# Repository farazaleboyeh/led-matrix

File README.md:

# Custom-Built Music Display

## Goal
The purpose of this project has been to extend my skills as a hardware engineer, specifically in regards to the development of embedded systems. Thus, I challenged myself to build a complete system from scratch that encompasses the entire development lifecycle. From schematic design and PCB layout in KiCad, to writing the C++ firmware for Wi-Fi networking, memory management, & custom LED multiplexing.

## Overview
Repository includes the firmwmare used to show the artwork of a currently streaming song from Spotify onto a custom-built 10x10 display, as well as all primary KiCad project files used to design the system itself. Some examples images of the display in its most recent state are available below.

<div align="center">
  <table>
    <tr>
      <td align="center">
        
        <br />
        <sub><em>Example 1, raw LEDs exposed.</em></sub>
      </td>
      <td align="center">
        
        <br />
        <sub><em>Example 2, raw LEDs exposed.</em></sub>
      </td>
    </tr>
    <tr>
      <td align="center">
        
        <br />
        <sub><em>Example 3, makeshift diffuser overlayed. </em></sub>
      </td>
      <td align="center">
      
        <br />
        <sub><em>Example 4, makeshift diffuser overlayed.</em></sub>
      </td>
    </tr>
  </table>
</div>

The system works by first calling Spotify's APIs to fetch all data regarding the user's playing music. From the given information, a link to the  album art is then used to store all JPEG data (as a stream of bytes) to an internal buffer. The TJpg Decoder library is used to decode the buffer as RGB565 data (locally), which perpetually reaches out to a separate callback function, which converts again to RGB888 and also writes to the display's back framebuffer. When the front and back framebuffers are swapped, a continuously firing interrupt displays the artwork by streaming the bitplanes (sequentially by time slice and physical row), to the display's shift registers. 

## Hardware 
### Comprehensive Component List
* 100 RGB LEDs, multiplexed
* 10 100Ω, 10 150Ω, 10 220Ω, & 10 1kΩ resistors
* 5 (74HC595) shift registers, daisy-chained.
* 10 PNP BJTs
* An ESP32-S3, development board
* A USB-C breakout board

### Core Physical Functionality
The display is driven by an ESP32 microcontroller, which is responsible for streaming color data to the chained shift registers, among other tasks. Transistors are present along all rows which act as high-side power switches between the main power rail and the shared anodes, so that the (output-limited) shift registers are not solely responsible for driving entire rows themselves. 1kΩ current-limiting resistors are present along rows to protect the shift registers and LEDs from overheating & overcurrent, with per-color resistors along each column to finely tune color output (100Ω for red columns, 150Ω, green, & 220Ω blue). Images of the schematic, PCB design, & soldered board are all shown below for reference.

<div align="center">
  
  <br />
  <sub><i>Schematic diagram, designed in KiCad.</i></sub>
</div>

<br />

<div align="center">
  
  <br />
  <sub><i>PCB layout, designed in KiCad.</i></sub>
</div>

<br />

<div align="center">
  
  <br />
  <sub><i>Soldered PCB, note that the breakout is still missing the screws and washers necessary for securing it to the board but is otherwise complete.</i></sub>
</div>

## Firmware 
### Core Logical Functionality

<div align="center">
  
  <br />
  <sub><i>UML sequence diagram, complete program flow.</i></sub>
</div>

### API Access
The basis of the project lies in interfacing with Spotify's APIs to receieve user data regarding their currently playing music. Every time the program begins running, and after a successful Wi-Fi connection is established, one of the first tasks to run is the retrieval of a new Access Token from Spotify's servers. As per the Spotify's requirements, Access Tokens are inherently ephemeral, expiring automatically every 3600 seconds (1 hour) regardless of scope. Thus, a function runs every 55 minutes to renew the Activation Token automatically, ensuring the display can be used for extended periods of time. 

There is not currently, however, any avenue for renewing the Refresh Tokens  automatically at the time of writing. Given they expire every 4 months, an implementation for such was not listed as high-enough priority but is in the works. 

### Interrupt-Driven Binary Code Modulation (BCM)
Instead of standard PWM, which would demand an unsustainable 2,550 SPI updates per frame (10 rows x 255 steps) and cause severe CPU starvation, the driver implements Binary Code Modulation via the microcontroller's hardware timer. By shifting only 8 exponentially weighted bitplanes per row (5µs, 10µs, 20µs, etc.), BCM slashes bus traffic by 97% to just 80 updates per frame, reconstructing full 8-bit color depth through visual persistence while leaving the CPU free for WiFi and JPEG decoding.

### Double Buffering
To prevent screen tearing during WiFi fetches or JPEG decoding: Operations draw to a back framebuffer (`draw_buffer`), `display.swap()` unpacks the back buffer into physical bitplanes (`bitplanes[10][8][5]`), & the ISR (`on_timer`) exclusively reads from the active bitplanes.

## Progress
A list of the main tasks in progress for this project:
* Upscaling the 8x8 artwork to 10x10
* Implementing animated song transitions
* Designing and 3D printing an enlosure and diffuser

A non-exhaustive list of ideas for future iterations of this project:
* LEDs & all other display hardware sitting on separate PCBs
* Playback controls (buttons, or other sensors for touchless playback)
* Transition firmware from Arduino framework to ESP-IDF with FreeRTOS

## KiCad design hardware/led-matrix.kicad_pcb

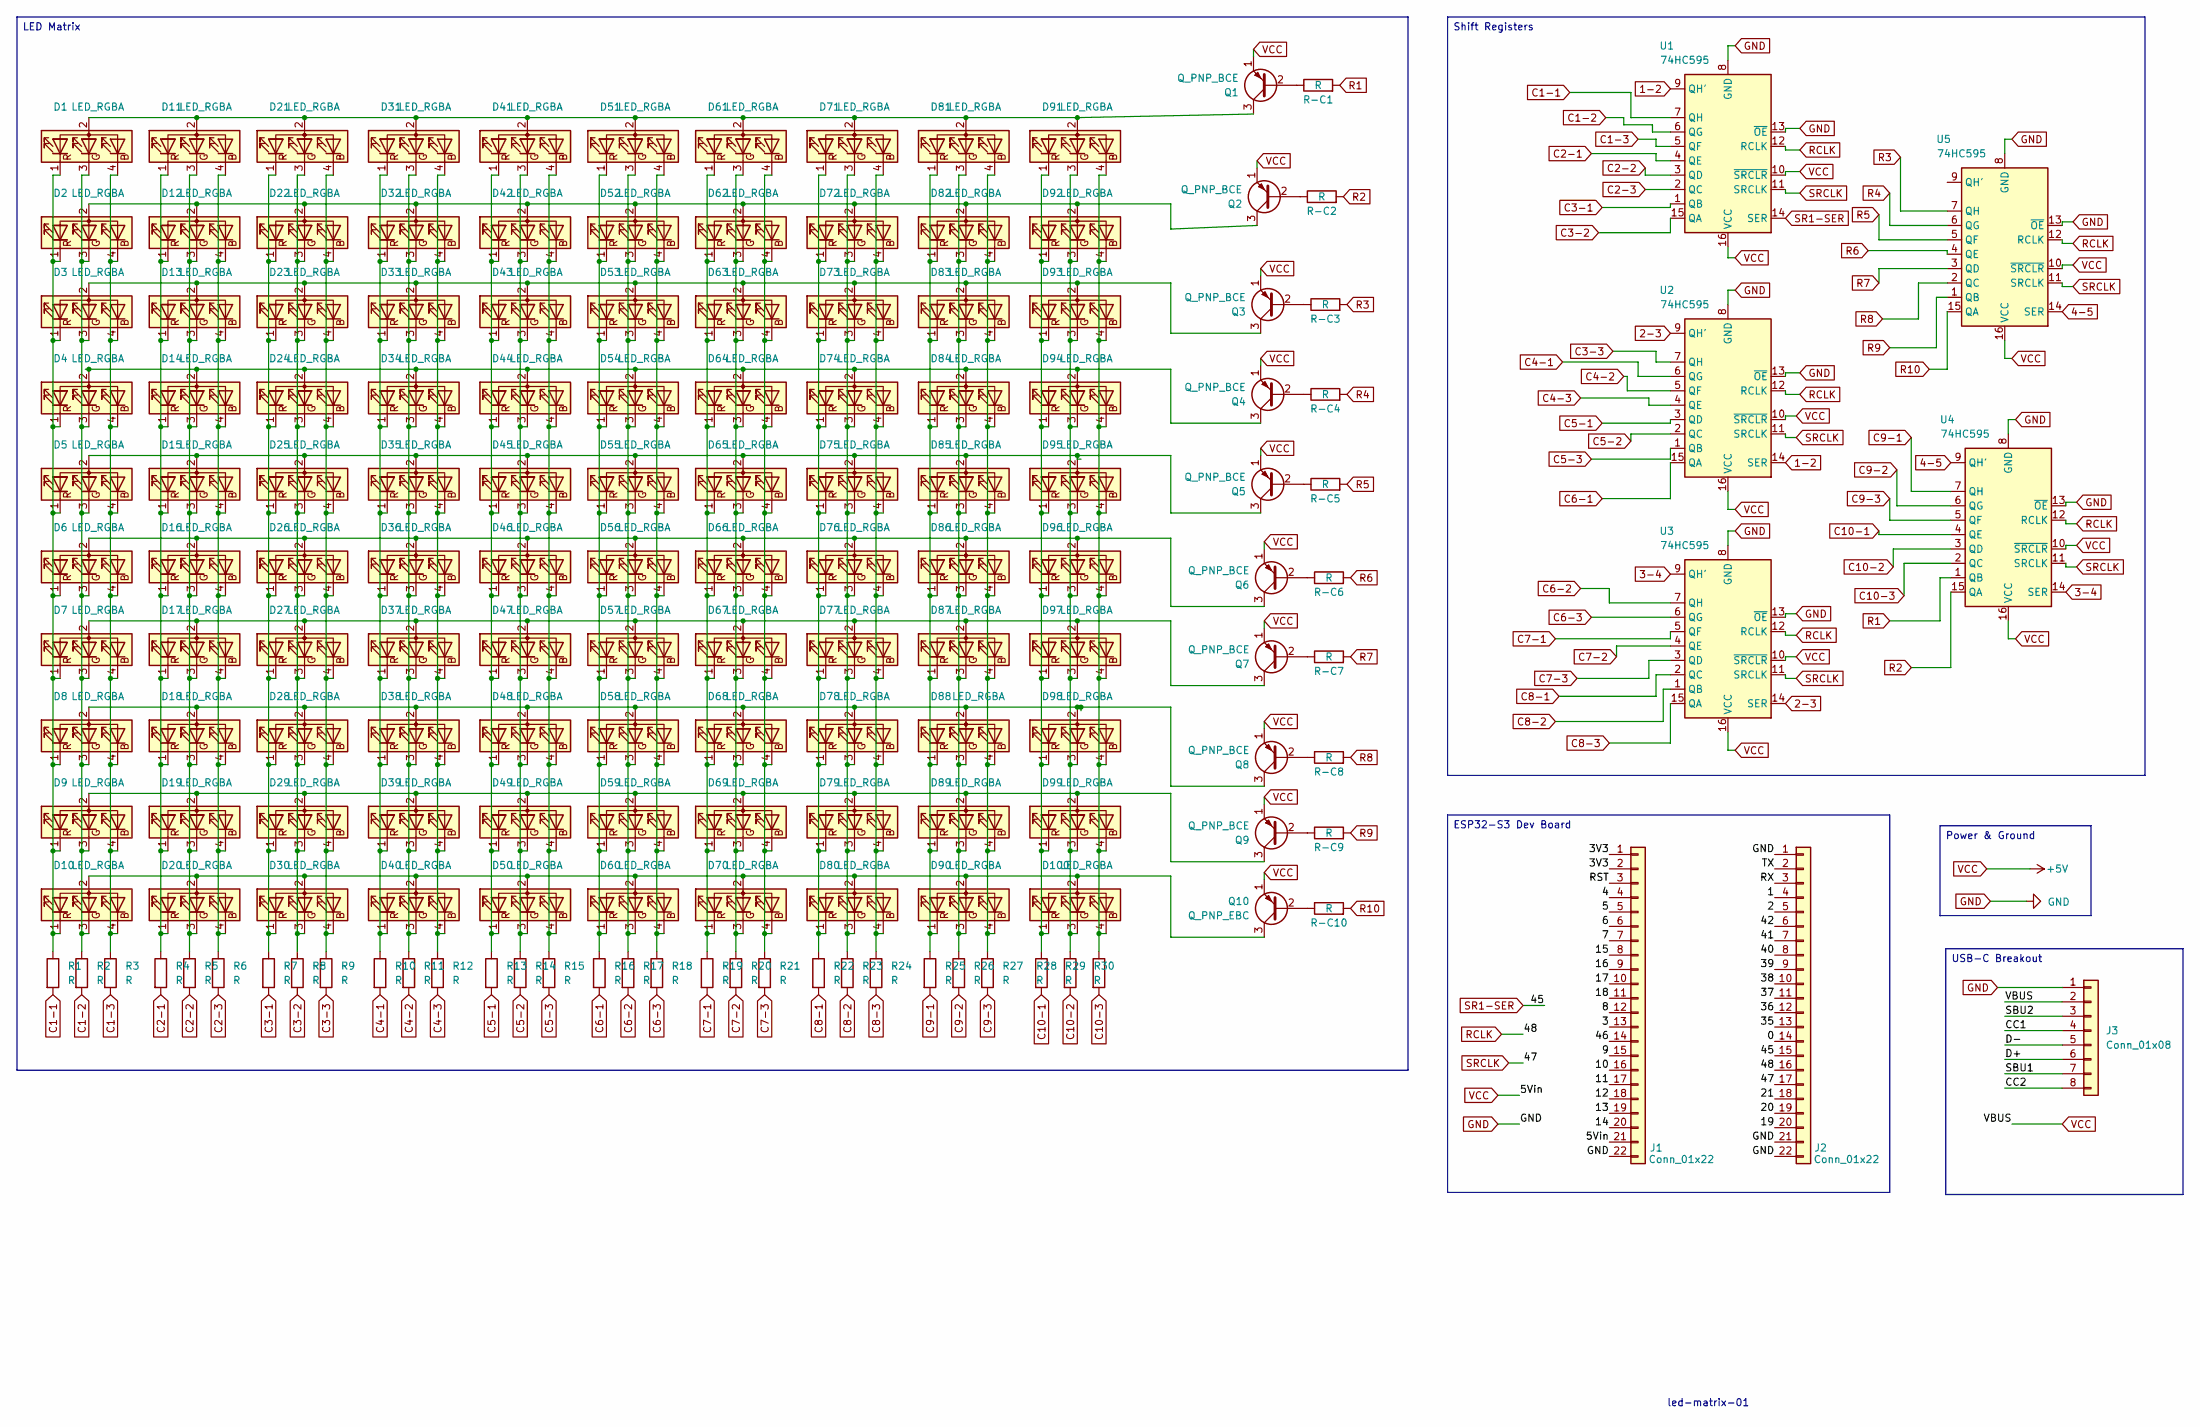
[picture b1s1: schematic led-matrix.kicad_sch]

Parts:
D1, D2, D3, D4, D5, D6, D7, D8, D9, D10, D11, D12, D13, D14, D15, D16, D17, D18, D19, D20, D21, D22, D23, D24, D25, D26, D27, D28, D29, D30, D31, D32, D33, D34, D35, D36, D37, D38, D39, D40, D41, D42, D43, D44, D45, D46, D47, D48, D49, D50, D51, D52, D53, D54, D55, D56, D57, D58, D59, D60, D61, D62, D63, D64, D65, D66, D67, D68, D69, D70, D71, D72, D73, D74, D75, D76, D77, D78, D79, D80, D81, D82, D83, D84, D85, D86, D87, D88, D89, D90, D91, D92, D93, D94, D95, D96, D97, D98, D99, D100: LED_RGBA; LED_D5.0mm-4_RGB_Wide_Pins
J1, J2: Conn_01x22; PinSocket_1x22_P2.54mm_Vertical
J3: Conn_01x08; PinSocket_1x08_P2.54mm_Vertical
Q1, Q2, Q3, Q4, Q5, Q6, Q7, Q8, Q9: Q_PNP_BCE; TO-92_Inline_Wide
Q10: Q_PNP_EBC; TO-92_Inline_Wide
R1, R2, R3, R4, R5, R6, R7, R8, R9, R10, R11, R12, R13, R14, R15, R16, R17, R18, R19, R20, R21, R22, R23, R24, R25, R26, R27, R28, R29, R30: R; R_Axial_DIN0207_L6.3mm_D2.5mm_P10.16mm_Horizontal
R-C1, R-C2, R-C3, R-C4, R-C5, R-C6, R-C7, R-C8, R-C9, R-C10: R; R_Axial_DIN0207_L6.3mm_D2.5mm_P10.16mm_Horizontal
U1, U2, U3, U4, U5: 74HC595; DIP794W45P254L1969H508Q16

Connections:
1-2: U1.9 (QH'), U2.14 (SER)
2-3: U2.9 (QH'), U3.14 (SER)
3-4: U3.9 (QH'), U4.14 (SER)
4-5: U4.9 (QH'), U5.14 (SER)
/0: J2.14
/1: J2.4
/2: J2.5
/3: J1.13
/3V3: J1.1, J1.2
/4: J1.4
/5: J1.5
/6: J1.6
/7: J1.7
/8: J1.12
/9: J1.15
/10: J1.16
/11: J1.17
/12: J1.18
/13: J1.19
/14: J1.20
/15: J1.8
/16: J1.9
/17: J1.10
/18: J1.11
/19: J2.20
/20: J2.19
/21: J2.18
/35: J2.13
/36: J2.12
/37: J2.11
/38: J2.10
/39: J2.9
/40: J2.8
/41: J2.7
/42: J2.6
/46: J1.14
/CC1: J3.4
/CC2: J3.8
/D+: J3.6
/D-: J3.5
/RST: J1.3
/RX: J2.3
/SBU1: J3.7
/SBU2: J3.3
/TX: J2.2
C1-1: R1.2, U1.7 (QH)
C1-2: R2.2, U1.6 (QG)
C1-3: R3.2, U1.5 (QF)
C2-1: R4.2, U1.4 (QE)
C2-2: R5.2, U1.3 (QD)
C2-3: R6.2, U1.2 (QC)
C3-1: R7.2, U1.1 (QB)
C3-2: R8.2, U1.15 (QA)
C3-3: R9.2, U2.7 (QH)
C4-1: R10.2, U2.6 (QG)
C4-2: R11.2, U2.5 (QF)
C4-3: R12.2, U2.4 (QE)
C5-1: R13.2, U2.3 (QD)
C5-2: R14.2, U2.2 (QC)
C5-3: R15.2, U2.1 (QB)
C6-1: R16.2, U2.15 (QA)
C6-2: R17.2, U3.7 (QH)
C6-3: R18.2, U3.6 (QG)
C7-1: R19.2, U3.5 (QF)
C7-2: R20.2, U3.4 (QE)
C7-3: R21.2, U3.3 (QD)
C8-1: R22.2, U3.2 (QC)
C8-2: R23.2, U3.1 (QB)
C8-3: R24.2, U3.15 (QA)
C9-1: R25.2, U4.7 (QH)
C9-2: R26.2, U4.6 (QG)
C9-3: R27.2, U4.5 (QF)
C10-1: R28.2, U4.4 (QE)
C10-2: R29.2, U4.3 (QD)
C10-3: R30.2, U4.2 (QC)
GND: J1.22, J2.1, J2.21, J2.22, J3.1, U1.8 (GND), U1.13 (~OE), U2.8 (GND), U2.13 (~OE), U3.8 (GND), U3.13 (~OE), U4.8 (GND), U4.13 (~OE), U5.8 (GND), U5.13 (~OE)
unnamed: D1.2 (A), D11.2 (A), D21.2 (A), D31.2 (A), D41.2 (A), D51.2 (A), D61.2 (A), D71.2 (A), D81.2 (A), D91.2 (A), Q1.3 (C)
unnamed: D1.4 (BK), D2.4 (BK), D3.4 (BK), D4.4 (BK), D5.4 (BK), D6.4 (BK), D7.4 (BK), D8.4 (BK), D9.4 (BK), D10.4 (BK), R3.1
unnamed: D1.3 (GK), D2.3 (GK), D3.3 (GK), D4.3 (GK), D5.3 (GK), D6.3 (GK), D7.3 (GK), D8.3 (GK), D9.3 (GK), D10.3 (GK), R2.1
unnamed: D1.1 (RK), D2.1 (RK), D3.1 (RK), D4.1 (RK), D5.1 (RK), D6.1 (RK), D7.1 (RK), D8.1 (RK), D9.1 (RK), D10.1 (RK), R1.1
unnamed: D10.2 (A), D20.2 (A), D30.2 (A), D40.2 (A), D50.2 (A), D60.2 (A), D70.2 (A), D80.2 (A), D90.2 (A), D100.2 (A), Q10.3 (C)
unnamed: D11.4 (BK), D12.4 (BK), D13.4 (BK), D14.4 (BK), D15.4 (BK), D16.4 (BK), D17.4 (BK), D18.4 (BK), D19.4 (BK), D20.4 (BK), R6.1
unnamed: D11.3 (GK), D12.3 (GK), D13.3 (GK), D14.3 (GK), D15.3 (GK), D16.3 (GK), D17.3 (GK), D18.3 (GK), D19.3 (GK), D20.3 (GK), R5.1
unnamed: D11.1 (RK), D12.1 (RK), D13.1 (RK), D14.1 (RK), D15.1 (RK), D16.1 (RK), D17.1 (RK), D18.1 (RK), D19.1 (RK), D20.1 (RK), R4.1
unnamed: D2.2 (A), D12.2 (A), D22.2 (A), D32.2 (A), D42.2 (A), D52.2 (A), D62.2 (A), D72.2 (A), D82.2 (A), D92.2 (A), Q2.3 (C)
unnamed: D3.2 (A), D13.2 (A), D23.2 (A), D33.2 (A), D43.2 (A), D53.2 (A), D63.2 (A), D73.2 (A), D83.2 (A), D93.2 (A), Q3.3 (C)
unnamed: D4.2 (A), D14.2 (A), D24.2 (A), D34.2 (A), D44.2 (A), D54.2 (A), D64.2 (A), D74.2 (A), D84.2 (A), D94.2 (A), Q4.3 (C)
unnamed: D5.2 (A), D15.2 (A), D25.2 (A), D35.2 (A), D45.2 (A), D55.2 (A), D65.2 (A), D75.2 (A), D85.2 (A), D95.2 (A), Q5.3 (C)
unnamed: D6.2 (A), D16.2 (A), D26.2 (A), D36.2 (A), D46.2 (A), D56.2 (A), D66.2 (A), D76.2 (A), D86.2 (A), D96.2 (A), Q6.3 (C)
unnamed: D7.2 (A), D17.2 (A), D27.2 (A), D37.2 (A), D47.2 (A), D57.2 (A), D67.2 (A), D77.2 (A), D87.2 (A), D97.2 (A), Q7.3 (C)
unnamed: D8.2 (A), D18.2 (A), D28.2 (A), D38.2 (A), D48.2 (A), D58.2 (A), D68.2 (A), D78.2 (A), D88.2 (A), D98.2 (A), Q8.3 (C)
unnamed: D9.2 (A), D19.2 (A), D29.2 (A), D39.2 (A), D49.2 (A), D59.2 (A), D69.2 (A), D79.2 (A), D89.2 (A), D99.2 (A), Q9.3 (C)
unnamed: D21.4 (BK), D22.4 (BK), D23.4 (BK), D24.4 (BK), D25.4 (BK), D26.4 (BK), D27.4 (BK), D28.4 (BK), D29.4 (BK), D30.4 (BK), R9.1
unnamed: D21.3 (GK), D22.3 (GK), D23.3 (GK), D24.3 (GK), D25.3 (GK), D26.3 (GK), D27.3 (GK), D28.3 (GK), D29.3 (GK), D30.3 (GK), R8.1
unnamed: D21.1 (RK), D22.1 (RK), D23.1 (RK), D24.1 (RK), D25.1 (RK), D26.1 (RK), D27.1 (RK), D28.1 (RK), D29.1 (RK), D30.1 (RK), R7.1
unnamed: D31.4 (BK), D32.4 (BK), D33.4 (BK), D34.4 (BK), D35.4 (BK), D36.4 (BK), D37.4 (BK), D38.4 (BK), D39.4 (BK), D40.4 (BK), R12.1
unnamed: D31.3 (GK), D32.3 (GK), D33.3 (GK), D34.3 (GK), D35.3 (GK), D36.3 (GK), D37.3 (GK), D38.3 (GK), D39.3 (GK), D40.3 (GK), R11.1
unnamed: D31.1 (RK), D32.1 (RK), D33.1 (RK), D34.1 (RK), D35.1 (RK), D36.1 (RK), D37.1 (RK), D38.1 (RK), D39.1 (RK), D40.1 (RK), R10.1
unnamed: D41.4 (BK), D42.4 (BK), D43.4 (BK), D44.4 (BK), D45.4 (BK), D46.4 (BK), D47.4 (BK), D48.4 (BK), D49.4 (BK), D50.4 (BK), R15.1
unnamed: D41.3 (GK), D42.3 (GK), D43.3 (GK), D44.3 (GK), D45.3 (GK), D46.3 (GK), D47.3 (GK), D48.3 (GK), D49.3 (GK), D50.3 (GK), R14.1
unnamed: D41.1 (RK), D42.1 (RK), D43.1 (RK), D44.1 (RK), D45.1 (RK), D46.1 (RK), D47.1 (RK), D48.1 (RK), D49.1 (RK), D50.1 (RK), R13.1
unnamed: D51.4 (BK), D52.4 (BK), D53.4 (BK), D54.4 (BK), D55.4 (BK), D56.4 (BK), D57.4 (BK), D58.4 (BK), D59.4 (BK), D60.4 (BK), R18.1
unnamed: D51.3 (GK), D52.3 (GK), D53.3 (GK), D54.3 (GK), D55.3 (GK), D56.3 (GK), D57.3 (GK), D58.3 (GK), D59.3 (GK), D60.3 (GK), R17.1
unnamed: D51.1 (RK), D52.1 (RK), D53.1 (RK), D54.1 (RK), D55.1 (RK), D56.1 (RK), D57.1 (RK), D58.1 (RK), D59.1 (RK), D60.1 (RK), R16.1
unnamed: D61.4 (BK), D62.4 (BK), D63.4 (BK), D64.4 (BK), D65.4 (BK), D66.4 (BK), D67.4 (BK), D68.4 (BK), D69.4 (BK), D70.4 (BK), R21.1
unnamed: D61.3 (GK), D62.3 (GK), D63.3 (GK), D64.3 (GK), D65.3 (GK), D66.3 (GK), D67.3 (GK), D68.3 (GK), D69.3 (GK), D70.3 (GK), R20.1
unnamed: D61.1 (RK), D62.1 (RK), D63.1 (RK), D64.1 (RK), D65.1 (RK), D66.1 (RK), D67.1 (RK), D68.1 (RK), D69.1 (RK), D70.1 (RK), R19.1
unnamed: D71.4 (BK), D72.4 (BK), D73.4 (BK), D74.4 (BK), D75.4 (BK), D76.4 (BK), D77.4 (BK), D78.4 (BK), D79.4 (BK), D80.4 (BK), R24.1
unnamed: D71.3 (GK), D72.3 (GK), D73.3 (GK), D74.3 (GK), D75.3 (GK), D76.3 (GK), D77.3 (GK), D78.3 (GK), D79.3 (GK), D80.3 (GK), R23.1
unnamed: D71.1 (RK), D72.1 (RK), D73.1 (RK), D74.1 (RK), D75.1 (RK), D76.1 (RK), D77.1 (RK), D78.1 (RK), D79.1 (RK), D80.1 (RK), R22.1
unnamed: D81.4 (BK), D82.4 (BK), D83.4 (BK), D84.4 (BK), D85.4 (BK), D86.4 (BK), D87.4 (BK), D88.4 (BK), D89.4 (BK), D90.4 (BK), R27.1
unnamed: D81.3 (GK), D82.3 (GK), D83.3 (GK), D84.3 (GK), D85.3 (GK), D86.3 (GK), D87.3 (GK), D88.3 (GK), D89.3 (GK), D90.3 (GK), R26.1
unnamed: D81.1 (RK), D82.1 (RK), D83.1 (RK), D84.1 (RK), D85.1 (RK), D86.1 (RK), D87.1 (RK), D88.1 (RK), D89.1 (RK), D90.1 (RK), R25.1
unnamed: D91.4 (BK), D92.4 (BK), D93.4 (BK), D94.4 (BK), D95.4 (BK), D96.4 (BK), D97.4 (BK), D98.4 (BK), D99.4 (BK), D100.4 (BK), R30.1
unnamed: D91.3 (GK), D92.3 (GK), D93.3 (GK), D94.3 (GK), D95.3 (GK), D96.3 (GK), D97.3 (GK), D98.3 (GK), D99.3 (GK), D100.3 (GK), R29.1
unnamed: D91.1 (RK), D92.1 (RK), D93.1 (RK), D94.1 (RK), D95.1 (RK), D96.1 (RK), D97.1 (RK), D98.1 (RK), D99.1 (RK), D100.1 (RK), R28.1
unnamed: Q1.2 (B), R-C1.1
unnamed: Q2.2 (B), R-C2.1
unnamed: Q3.2 (B), R-C3.1
unnamed: Q4.2 (B), R-C4.1
unnamed: Q5.2 (B), R-C5.1
unnamed: Q6.2 (B), R-C6.1
unnamed: Q7.2 (B), R-C7.1
unnamed: Q8.2 (B), R-C8.1
unnamed: Q9.2 (B), R-C9.1
unnamed: Q10.2 (B), R-C10.1
R1: R-C1.2, U4.1 (QB)
R2: R-C2.2, U4.15 (QA)
R3: R-C3.2, U5.7 (QH)
R4: R-C4.2, U5.6 (QG)
R5: R-C5.2, U5.5 (QF)
R6: R-C6.2, U5.4 (QE)
R7: R-C7.2, U5.3 (QD)
R8: R-C8.2, U5.2 (QC)
R9: R-C9.2, U5.1 (QB)
R10: R-C10.2, U5.15 (QA)
RCLK: J2.16, U1.12 (RCLK), U2.12 (RCLK), U3.12 (RCLK), U4.12 (RCLK), U5.12 (RCLK)
SR1-SER: J2.15, U1.14 (SER)
SRCLK: J2.17, U1.11 (SRCLK), U2.11 (SRCLK), U3.11 (SRCLK), U4.11 (SRCLK), U5.11 (SRCLK)
VCC: J1.21, J3.2, Q1.1 (E), Q2.1 (E), Q3.1 (E), Q4.1 (E), Q5.1 (E), Q6.1 (E), Q7.1 (E), Q8.1 (E), Q9.1 (E), Q10.1 (E), U1.10 (~SRCLR), U1.16 (VCC), U2.10 (~SRCLR), U2.16 (VCC), U3.10 (~SRCLR), U3.16 (VCC), U4.10 (~SRCLR), U4.16 (VCC), U5.10 (~SRCLR), U5.16 (VCC)

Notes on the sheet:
led-matrix-01
USB-C Breakout
Shift Registers
ESP32-S3 Dev Board
LED Matrix
Power & Ground

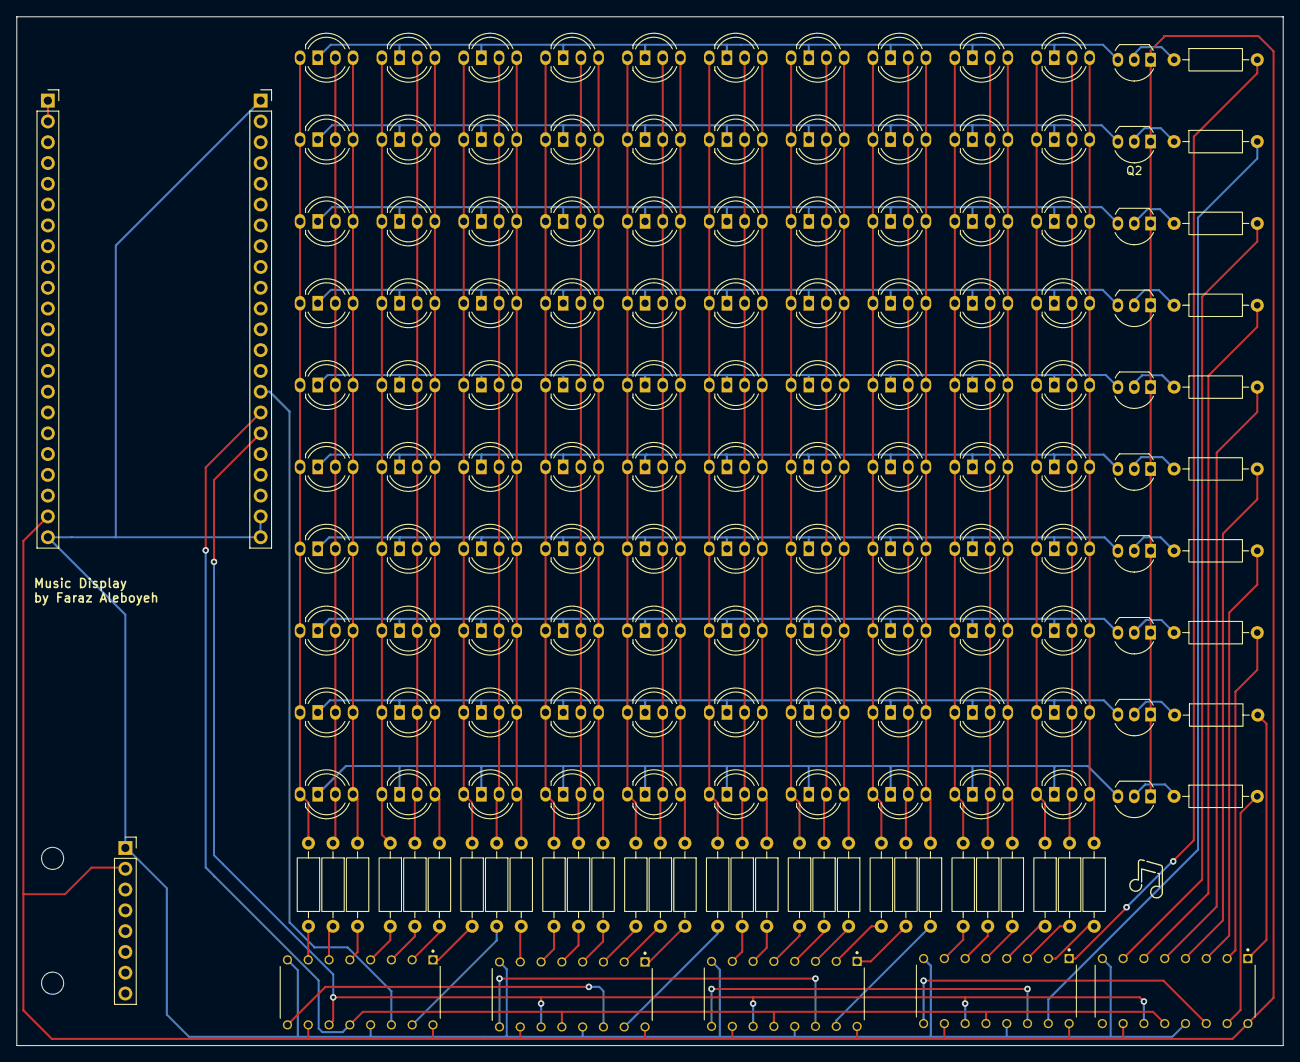
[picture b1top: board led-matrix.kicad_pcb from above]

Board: 2 copper layers, 154.7 x 125.7 mm, 158 parts (0 on the bottom side), 100 nets.

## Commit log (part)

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2026-05-22 Commit #1
